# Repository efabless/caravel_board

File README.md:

# Caravel Board

This repo provides firmware examples, flash programming and diagnostic tools for testing
Open MPW and chipIgnite projects using Caravel.  It also provides schematics, layout and gerber files for PCB evaluation and breakout boards.

## MPW-2 & MPW-3 Project Owners

See the README for the the Nucleo automated [test setup here](firmware/mpw2-5/nucleo)

## chipIgnite Projects (including Stanford)

See the README for testing projects here -- https://github.com/efabless/caravel_board/tree/main/firmware/chipignite#readme

## Firmware

You will need python 3.6 or later.  

To program Caravel, connect the evaluation board using a USB micro B connector.

```bash
pip3 install pyftdi

cd firmware/blink

make clean flash
```

### Install Toolchain for Compiling Code

#### For Mac

https://github.com/riscv/homebrew-riscv

#### For Linux

https://github.com/riscv/riscv-gnu-toolchain

### Diagnostics

Makefiles in the firmware project directories use 

> firmware/chipignite/util/caravel_hkflash.py 

to program the flash on the board through Caravel's housekeeping SPI interface.

> firmware/chipignite/util/caravel_hkdebug.py 

provides menu-driven debug through the housekeeping SPI interface for Caravel.

## Hardware

The current evaluation board for Caravel can be [found here](hardware/development/caravel-dev-v5-M.2)

- The clock is driven by X1 with a frequency of 10MHz. To drive the clock with custom frequency, disable X1 through J6 and use the external pin for `xclk`
- The voltage regulator U5 and U6 supply `1.8V` and `3.3V` through J8 and J9. The traces have to be cut if they are supplied externally.
- `vccd1` is connected to `1.8V` through J3. The trace has to be cut if it is supplied externally
- `vddio` is connected to `3.3V` through J5. The trace has to be cut if it is supplied externally

The most updated breakout board for Caravel can be found [here](hardware/breakout/caravel-M.2-card-QFN)

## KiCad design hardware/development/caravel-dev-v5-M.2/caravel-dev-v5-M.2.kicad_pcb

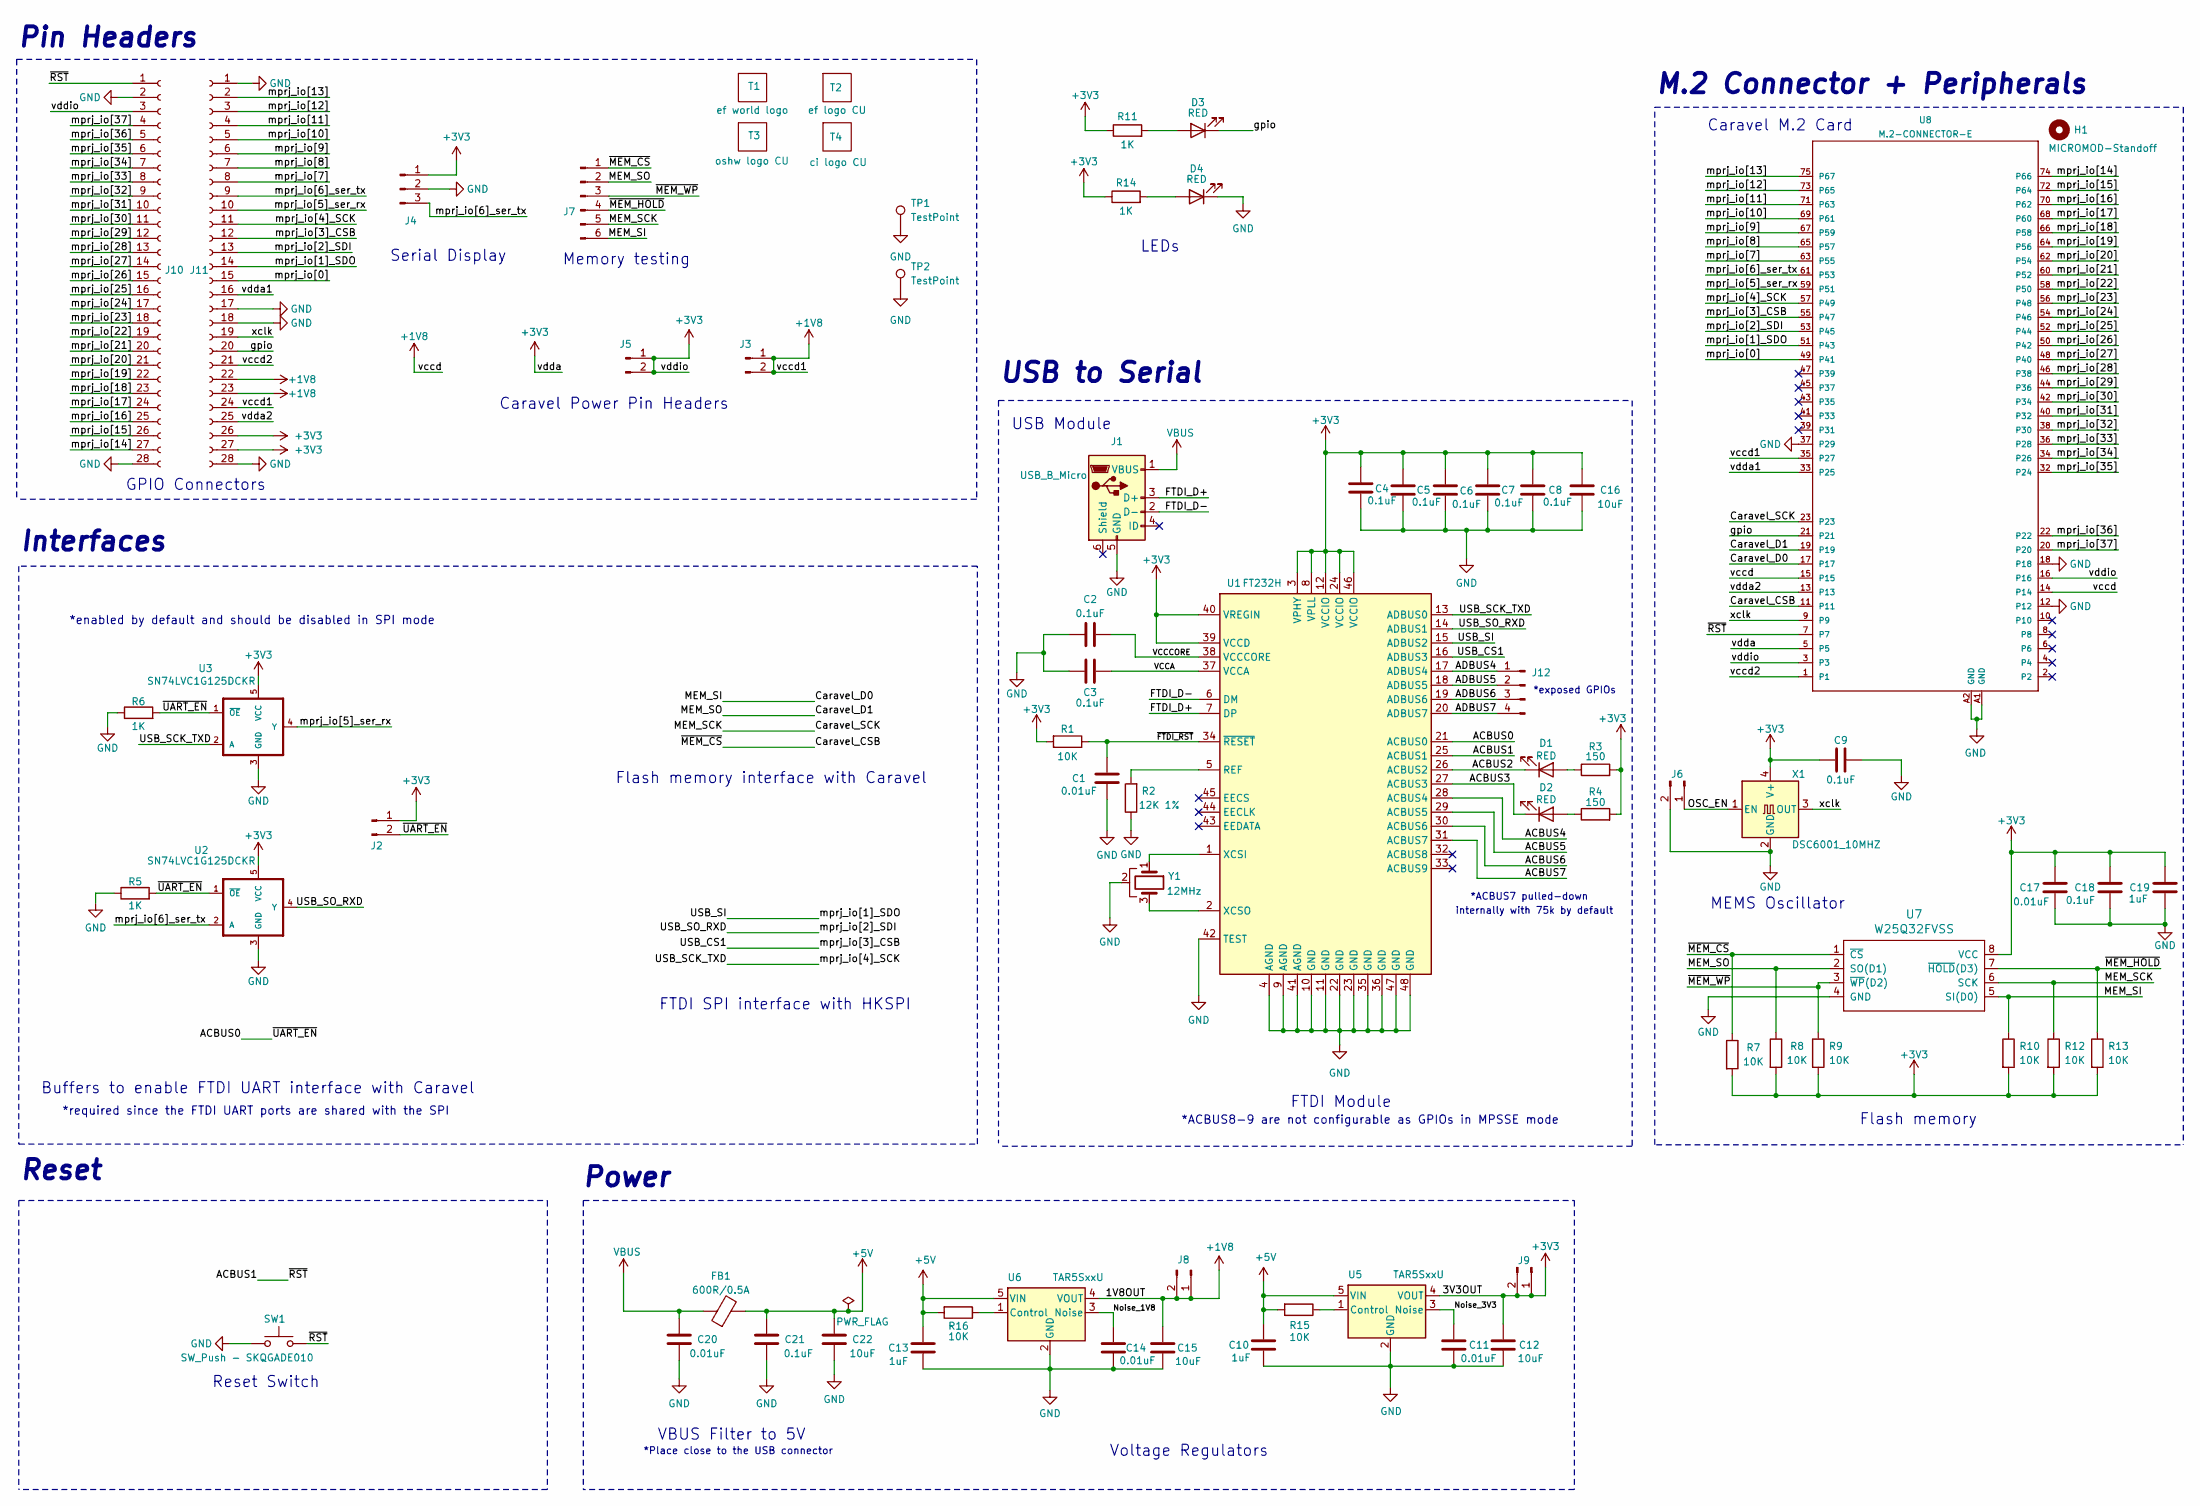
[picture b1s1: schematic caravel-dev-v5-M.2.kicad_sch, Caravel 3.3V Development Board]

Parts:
C1, C11, C14, C17, C20: 0.01uF; C_0805_2012Metric; Part # C0805C103K5RAC7411
C2, C3, C4, C5, C6, C7, C8, C9, C18, C21: 0.1uF; C_0805_2012Metric; Part # C0805C104K5RAC7411
C10, C13, C19: 1uF; C_0805_2012Metric; Part # 885012207103
C12, C15, C16, C22: 10uF; C_0805_2012Metric; Part # CL21B106KAYQNNE
D1, D2, D3, D4: RED; LED_1206_3216Metric; Part # LTST-C230KRKT
FB1: 600R/0.5A; L_0805_2012Metric; Part # 7427920415
H1: MICROMOD-Standoff; MicroMod-Standoff
J1: USB_B_Micro; FCI_10118193-0001LF; Part # 10118193-0001LF
J2, J3, J5, J6, J8, J9: Conn_01x02_Pin; PinHeader_1x02_P2.54mm_Vertical
J4: Conn_01x03_Pin; PinHeader_1x03_P2.54mm_Vertical
J7: Conn_01x06_Pin; PinHeader_1x06_P2.54mm_Vertical
J10, J11: Conn_01x28_Pin; PinHeader_1x28_P2.54mm_Vertical
J12: Conn_01x04_Pin; PinHeader_1x04_P2.54mm_Vertical
R1, R7, R8, R9, R10, R12, R13, R15, R16: 10K; R_0805_2012Metric; Part # RC0805FR-0710KL
R2: 12K 1%; R_0805_2012Metric; Part # RMCF0805FT12K0
R3, R4: 150; R_0805_2012Metric; Part # RNCP0805FTD150R
R5, R6, R11, R14: 1K; R_0805_2012Metric; Part # RC0805FR-071KL
SW1: SW_Push - SKQGADE010; SW4-SMD-5.2X5.2X1.5MM
T1: ef world logo; logo_large
T2: ef logo CU; ef_logo-cu
T3: oshw logo CU; oshw-logo
T4: ci logo CU; chipIgnite_logo
TP1, TP2: TestPoint; TestPoint_Bridge_Pitch2.54mm_Drill1.0mm
U1: FT232H; QFN-48-1EP_8x8mm_P0.5mm_EP6.2x6.2mm; Part # FT232H
U2, U3: SN74LVC1G125DCKR; SOT65P210X110-5N; Part # SN74LVC1G125DCKR
U5: TAR5SxxU; SOT-353F; Part # TAR5S33UTE85LF
U6: TAR5SxxU; SOT-353F; Part # TAR5S18U-TE85L-F
U7: W25Q32FVSS; SOIC127P790X216-8N; Part # W25Q32JVSSIQ
U8: M.2-CONNECTOR-E
X1: DSC6001_10MHZ; DSC6001JE1A-010.0000; Part # DSC6001JI1B
Y1: 12MHz; CSTNE12M0GH5L000R0; Part # CSTNE12M0GH5L000R0

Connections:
+1V8: C15.2, J3.1, J3.2, J8.1, J8.2, J11.22, J11.23, J11.24, U6.4 (VOUT), U8.14, U8.15, U8.35 (P27)
+3V3: C4.2, C5.2, C6.2, C7.2, C8.2, C9.2, C12.2, C16.1, C17.2, C18.1, C19.1, J2.1, J4.1, J5.1, J5.2, J9.1, J9.2, J10.3, J11.26, J11.27, R1.2, R3.2, R4.2, R7.2, R8.2, R9.2, R10.2, R11.1, R12.2, R13.2, R14.1, U1.3 (VPHY), U1.8 (VPLL), U1.12 (VCCIO), U1.24 (VCCIO), U1.39 (VCCD), U1.40 (VREGIN), U1.46 (VCCIO), U2.5 (VCC), U3.5 (VCC), U5.4 (VOUT), U7.8 (VCC), U8.3, U8.5, U8.16, X1.4 (V+)
+5V: C10.2, C13.2, C21.2, C22.2, FB1.2, R15.2, R16.2, U5.5 (VIN), U6.5 (VIN)
/ACBUS0: J2.2, R5.2, R6.2, U1.21 (ACBUS0), U2.1 (~OE), U3.1 (~OE)
/ACBUS1: J10.1, SW1.1, U1.25 (ACBUS1), U8.7
/ACBUS2: D1.1 (K), U1.26 (ACBUS2)
/ACBUS3: D2.1 (K), U1.27 (ACBUS3)
/ACBUS4: U1.28 (ACBUS4)
/ACBUS5: U1.29 (ACBUS5)
/ACBUS6: U1.30 (ACBUS6)
/ACBUS7: U1.31 (ACBUS7)
/ADBUS4: J12.1, U1.17 (ADBUS4)
/ADBUS5: J12.2, U1.18 (ADBUS5)
/ADBUS6: J12.3, U1.19 (ADBUS6)
/ADBUS7: J12.4, U1.20 (ADBUS7)
/Caravel_CSB: J7.1, R7.1, U7.1 (~CS), U8.11
/Caravel_D0: J7.6, R10.1, U7.5 (SI(D0)), U8.17
/Caravel_D1: J7.2, R8.1, U7.2 (SO(D1)), U8.19
/Caravel_SCK: J7.5, R12.1, U7.6 (SCK), U8.23
/FTDI_D+: J1.3 (D+), U1.7 (DP)
/FTDI_D-: J1.2 (D-), U1.6 (DM)
/Noise_1V8: C14.1, U6.3 (Noise)
/Noise_3V3: C11.1, U5.3 (Noise)
/OSC_EN: J6.1, X1.1 (EN)
/USB_CS1: J11.12, U1.16 (ADBUS3), U8.55 (P47)
/USB_SCK_TXD: J11.11, U1.13 (ADBUS0), U3.2 (A), U8.57 (P49)
/USB_SI: J11.14, U1.15 (ADBUS2), U8.51 (P43)
/USB_SO_RXD: J11.13, U1.14 (ADBUS1), U2.4 (Y), U8.53 (P45)
/VCCA: C3.2, U1.37 (VCCA)
/VCCCORE: C2.2, U1.38 (VCCCORE)
/gpio: D3.1 (K), J11.20, U8.21
/mprj_io[0]: J11.15, U8.49 (P41)
/mprj_io[5]_ser_rx: J11.10, U3.4 (Y), U8.59 (P51)
/mprj_io[6]_ser_tx: J4.3, J11.9, U2.2 (A), U8.61 (P53)
/mprj_io[7]: J11.8, U8.63 (P55)
/mprj_io[8]: J11.7, U8.65 (P57)
/mprj_io[9]: J11.6, U8.67 (P59)
/mprj_io[10]: J11.5, U8.69 (P61)
/mprj_io[11]: J11.4, U8.71 (P63)
/mprj_io[12]: J11.3, U8.73 (P65)
/mprj_io[13]: J11.2, U8.75 (P67)
/mprj_io[14]: J10.27, U8.74 (P66)
/mprj_io[15]: J10.26, U8.72 (P64)
/mprj_io[16]: J10.25, U8.70 (P62)
/mprj_io[17]: J10.24, U8.68 (P60)
/mprj_io[18]: J10.23, U8.66 (P58)
/mprj_io[19]: J10.22, U8.64 (P56)
/mprj_io[20]: J10.21, U8.62 (P54)
/mprj_io[21]: J10.20, U8.60 (P52)
/mprj_io[22]: J10.19, U8.58 (P50)
/mprj_io[23]: J10.18, U8.56 (P48)
/mprj_io[24]: J10.17, U8.54 (P46)
/mprj_io[25]: J10.16, U8.52 (P44)
/mprj_io[26]: J10.15, U8.50 (P42)
/mprj_io[27]: J10.14, U8.48 (P40)
/mprj_io[28]: J10.13, U8.46 (P38)
/mprj_io[29]: J10.12, U8.44 (P36)
/mprj_io[30]: J10.11, U8.42 (P34)
/mprj_io[31]: J10.10, U8.40 (P32)
/mprj_io[32]: J10.9, U8.38 (P30)
/mprj_io[33]: J10.8, U8.36 (P28)
/mprj_io[34]: J10.7, U8.34 (P26)
/mprj_io[35]: J10.6, U8.32 (P24)
/mprj_io[36]: J10.5, U8.22
/mprj_io[37]: J10.4, U8.20
/vccd2: J11.21, U8.1
/vdda1: J11.16, U8.33 (P25)
/vdda2: J11.25, U8.13
/xclk: J11.19, U8.9, X1.3 (OUT)
/~FTDI_RST: C1.2, R1.1, U1.34 (~RESET)
/~MEM_HOLD: J7.4, R13.1, U7.7 (~HOLD(D3))
/~MEM_WP: J7.3, R9.1, U7.3 (~WP(D2))
GND: C1.1, C2.1, C3.1, C4.1, C5.1, C6.1, C7.1, C8.1, C9.1, C10.1, C11.2, C12.1, C13.1, C14.2, C15.1, C16.2, C17.1, C18.2, C19.2, C20.2, C21.1, C22.1, D4.1 (K), J1.5 (GND), J4.2, J6.2, J10.2, J10.28, J11.1, J11.17, J11.18, J11.28, R2.1, R5.1, R6.1, SW1.2, TP1.1, TP2.1, U1.4 (AGND), U1.9 (AGND), U1.10 (GND), U1.11 (GND), U1.22 (GND), U1.23 (GND), U1.35 (GND), U1.36 (GND), U1.41 (AGND), U1.42 (TEST), U1.47 (GND), U1.48 (GND), U2.3 (GND), U3.3 (GND), U5.2 (GND), U6.2 (GND), U7.4 (GND), U8.12, U8.18, U8.37 (P29), U8.A1 (GND), U8.A2 (GND), X1.2 (GND), Y1.2
unnamed: D1.2 (A), R3.1
unnamed: D2.2 (A), R4.1
unnamed: D3.2 (A), R11.2
unnamed: D4.2 (A), R14.2
unnamed: R2.2, U1.5 (REF)
unnamed: U1.1 (XCSI), Y1.1
unnamed: U1.2 (XCSO), Y1.3
unnamed: R15.1, U5.1 (Control)
unnamed: R16.1, U6.1 (Control)
VBUS: C20.1, FB1.1, J1.1 (VBUS)

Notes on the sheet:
USB to Serial
USB Module
MEMS Oscillator
*Place close to the USB connector
Flash memory interface with Caravel
Caravel Power Pin Headers
GPIO Connectors
*required since the FTDI UART ports are shared with the SPI
LEDs
Flash memory
Serial Display
Buffers to enable FTDI UART interface with Caravel
M.2 Connector + Peripherals
*enabled by default and should be disabled in SPI mode
*exposed GPIOs
Power
Pin Headers
VBUS Filter to 5V
Interfaces
Voltage Regulators
*ACBUS8-9 are not configurable as GPIOs in MPSSE mode
Reset Switch
Memory testing
*ACBUS7 pulled-down
internally with 75k by default
FTDI SPI interface with HKSPI
FTDI Module
Reset
Caravel M.2 Card

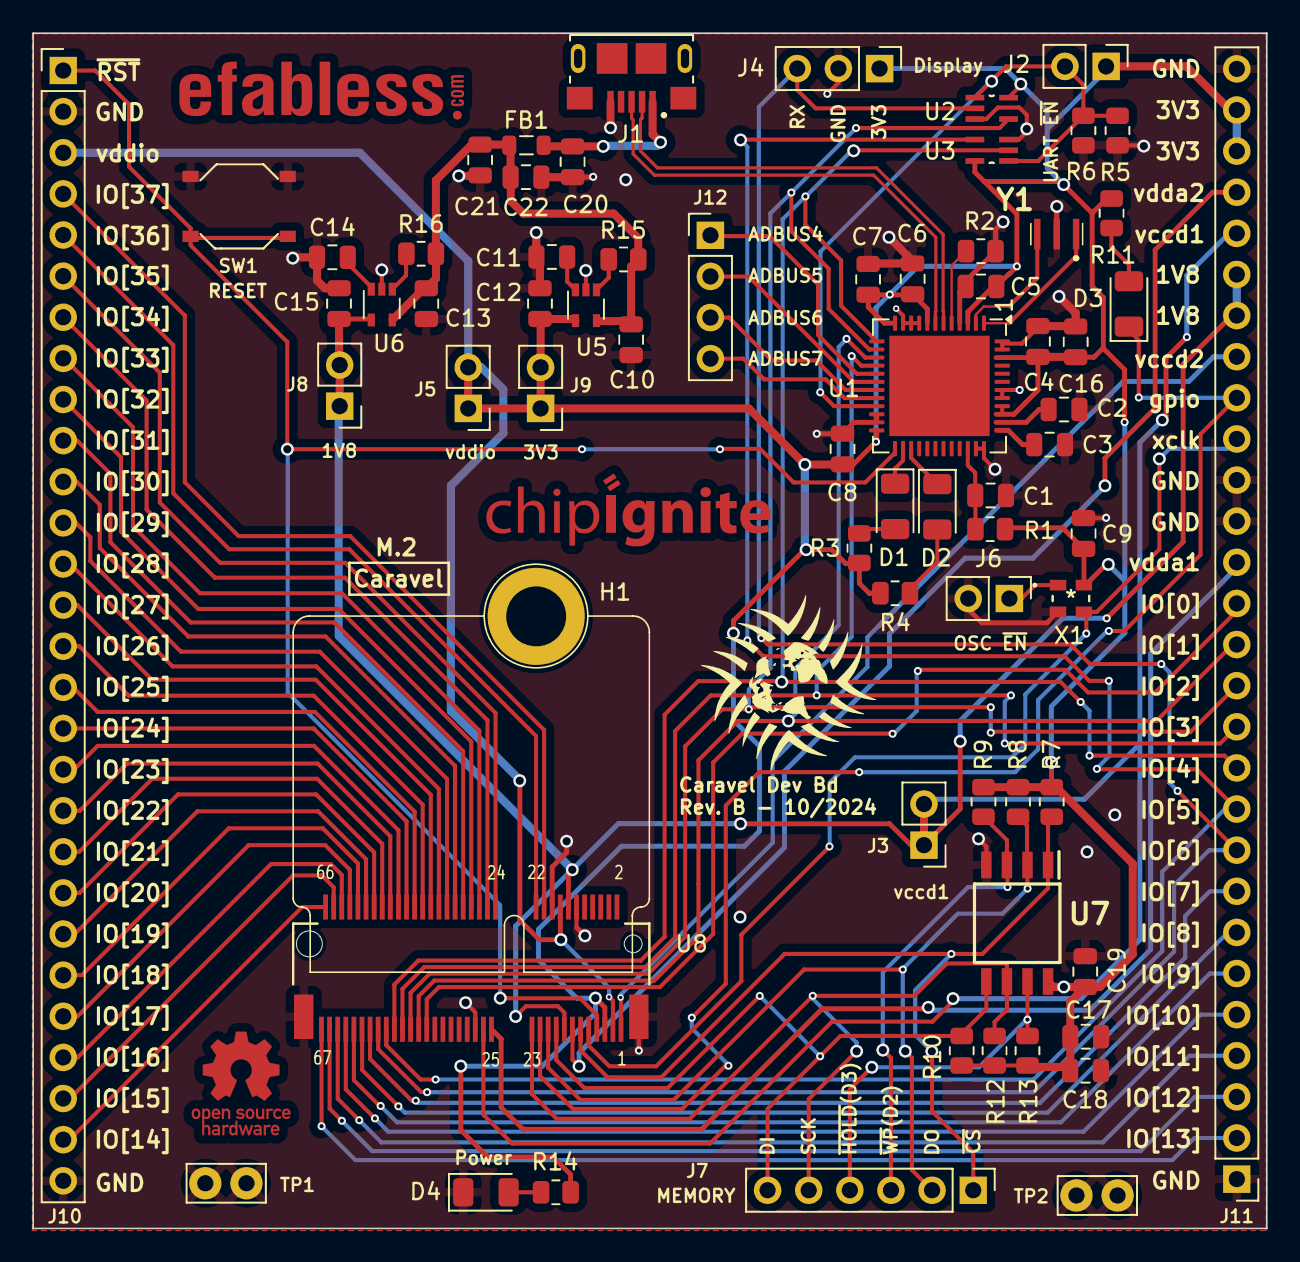
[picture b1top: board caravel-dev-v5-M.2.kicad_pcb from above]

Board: 2 copper layers, 76.2 x 73.8 mm, 72 parts (0 on the bottom side), 79 nets.

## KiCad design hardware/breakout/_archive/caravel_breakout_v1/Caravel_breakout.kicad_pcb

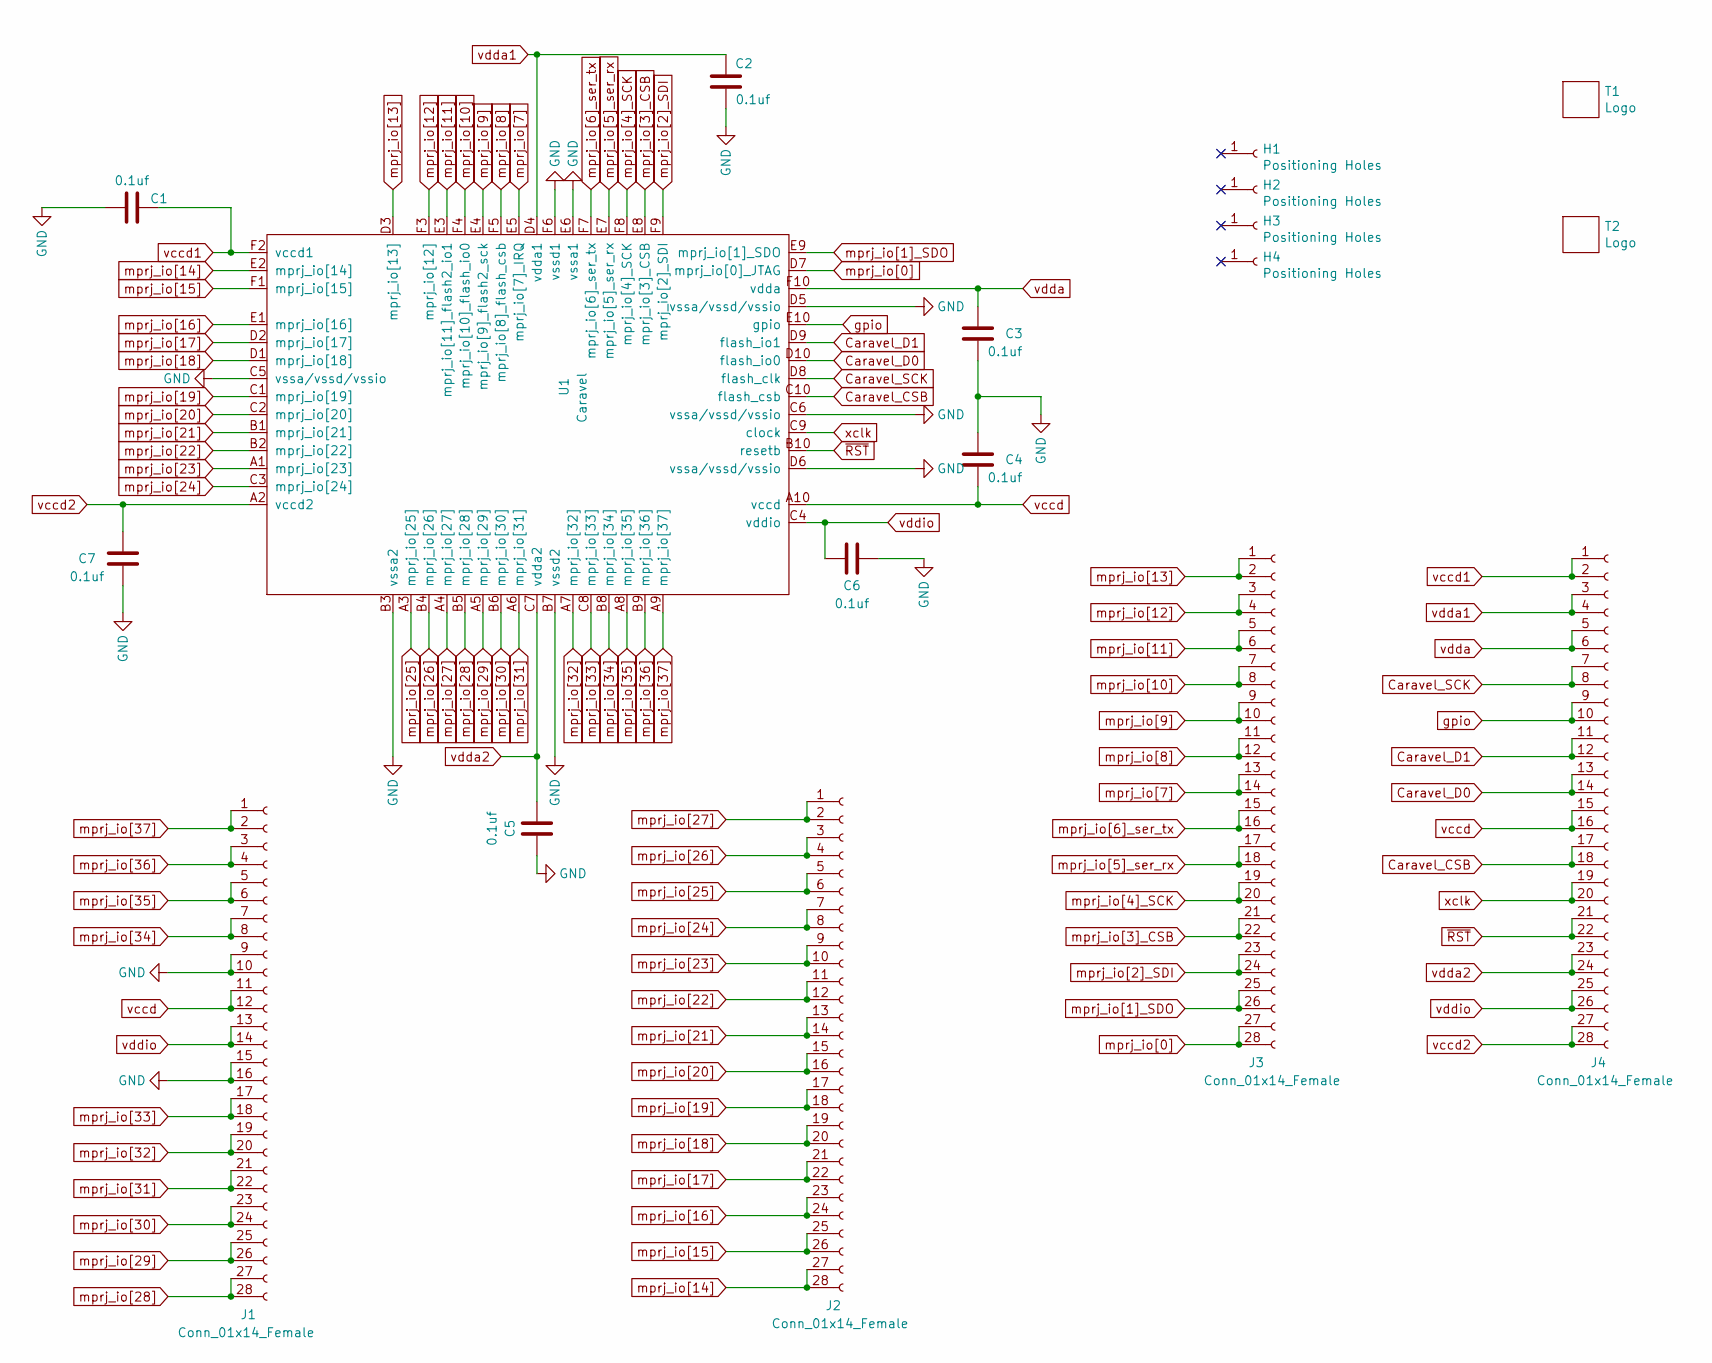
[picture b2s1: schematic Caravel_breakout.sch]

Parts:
C1, C2, C3, C4, C5, C6, C7: 0.1uf; C_0603_1608Metric
H1, H2, H3, H4: Positioning Holes; MountingHole_2.2mm_M2_ISO7380_Pad
J1, J2, J3, J4: Conn_01x14_Female; PinHeader_2x14_P1.27mm_Vertical
T1: Logo; logo
T2: Logo; ef_logo
U1: Caravel; Caravel_WCSP

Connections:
Caravel_CSB: J4.17, J4.18, U1.C10 (flash_csb)
Caravel_D0: J4.13, J4.14, U1.D10 (flash_io0)
Caravel_D1: J4.11, J4.12, U1.D9 (flash_io1)
Caravel_SCK: J4.7, J4.8, U1.D8 (flash_clk)
GND: C1.1, C2.2, C3.2, C4.1, C5.1, C6.1, C7.1, J1.9, J1.10, J1.15, J1.16, U1.B3 (vssa2), U1.B7 (vssd2), U1.C5 (vssa/vssd/vssio), U1.C6 (vssa/vssd/vssio), U1.D5 (vssa/vssd/vssio), U1.D6 (vssa/vssd/vssio), U1.E6 (vssa1), U1.F6 (vssd1)
gpio: J4.9, J4.10, U1.E10 (gpio)
mprj_io[0]: J3.27, J3.28, U1.D7 (mprj_io[0]_JTAG)
mprj_io[1]_SDO: J3.25, J3.26, U1.E9 (mprj_io[1]_SDO)
mprj_io[2]_SDI: J3.23, J3.24, U1.F9 (mprj_io[2]_SDI)
mprj_io[3]_CSB: J3.21, J3.22, U1.E8 (mprj_io[3]_CSB)
mprj_io[4]_SCK: J3.19, J3.20, U1.F8 (mprj_io[4]_SCK)
mprj_io[5]_ser_rx: J3.17, J3.18, U1.E7 (mprj_io[5]_ser_rx)
mprj_io[6]_ser_tx: J3.15, J3.16, U1.F7 (mprj_io[6]_ser_tx)
mprj_io[7]: J3.13, J3.14, U1.E5 (mprj_io[7]_IRQ)
mprj_io[8]: J3.11, J3.12, U1.F5 (mprj_io[8]_flash_csb)
mprj_io[9]: J3.9, J3.10, U1.E4 (mprj_io[9]_flash2_sck)
mprj_io[10]: J3.7, J3.8, U1.F4 (mprj_io[10]_flash_io0)
mprj_io[11]: J3.5, J3.6, U1.E3 (mprj_io[11]_flash2_io1)
mprj_io[12]: J3.3, J3.4, U1.F3 (mprj_io[12])
mprj_io[13]: J3.1, J3.2, U1.D3 (mprj_io[13])
mprj_io[14]: J2.27, J2.28, U1.E2 (mprj_io[14])
mprj_io[15]: J2.25, J2.26, U1.F1 (mprj_io[15])
mprj_io[16]: J2.23, J2.24, U1.E1 (mprj_io[16])
mprj_io[17]: J2.21, J2.22, U1.D2 (mprj_io[17])
mprj_io[18]: J2.19, J2.20, U1.D1 (mprj_io[18])
mprj_io[19]: J2.17, J2.18, U1.C1 (mprj_io[19])
mprj_io[20]: J2.15, J2.16, U1.C2 (mprj_io[20])
mprj_io[21]: J2.13, J2.14, U1.B1 (mprj_io[21])
mprj_io[22]: J2.11, J2.12, U1.B2 (mprj_io[22])
mprj_io[23]: J2.9, J2.10, U1.A1 (mprj_io[23])
mprj_io[24]: J2.7, J2.8, U1.C3 (mprj_io[24])
mprj_io[25]: J2.5, J2.6, U1.A3 (mprj_io[25])
mprj_io[26]: J2.3, J2.4, U1.B4 (mprj_io[26])
mprj_io[27]: J2.1, J2.2, U1.A4 (mprj_io[27])
mprj_io[28]: J1.27, J1.28, U1.B5 (mprj_io[28])
mprj_io[29]: J1.25, J1.26, U1.A5 (mprj_io[29])
mprj_io[30]: J1.23, J1.24, U1.B6 (mprj_io[30])
mprj_io[31]: J1.21, J1.22, U1.A6 (mprj_io[31])
mprj_io[32]: J1.19, J1.20, U1.A7 (mprj_io[32])
mprj_io[33]: J1.17, J1.18, U1.C8 (mprj_io[33])
mprj_io[34]: J1.7, J1.8, U1.B8 (mprj_io[34])
mprj_io[35]: J1.5, J1.6, U1.A8 (mprj_io[35])
mprj_io[36]: J1.3, J1.4, U1.B9 (mprj_io[36])
mprj_io[37]: J1.1, J1.2, U1.A9 (mprj_io[37])
vccd: C4.2, J1.11, J1.12, J4.15, J4.16, U1.A10 (vccd)
vccd1: C1.2, J4.1, J4.2, U1.F2 (vccd1)
vccd2: C7.2, J4.27, J4.28, U1.A2 (vccd2)
vdda: C3.1, J4.5, J4.6, U1.F10 (vdda)
vdda1: C2.1, J4.3, J4.4, U1.D4 (vdda1)
vdda2: C5.2, J4.23, J4.24, U1.C7 (vdda2)
vddio: C6.2, J1.13, J1.14, J4.25, J4.26, U1.C4 (vddio)
xclk: J4.19, J4.20, U1.C9 (clock)
~RST: J4.21, J4.22, U1.B10 (resetb)

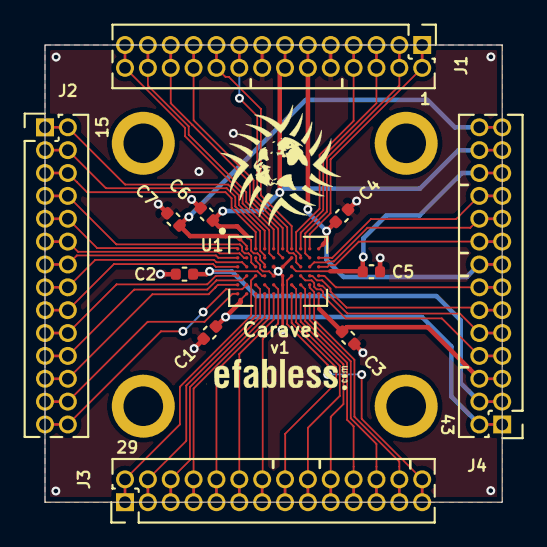
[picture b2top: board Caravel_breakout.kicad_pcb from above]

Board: 2 copper layers, 25.4 x 25.4 mm, 18 parts (0 on the bottom side), 53 nets.

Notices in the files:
parts and their libraries:
License: Apache-2.0
Copyright 2016 Accelerated Designs. All rights reserved.
